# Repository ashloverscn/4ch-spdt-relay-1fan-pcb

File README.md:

# 4ch-spdt-relay-1fan-pcb
4ch-spdt-relay-1fan-pcb

firmware written in arduino :

https://github.com/ashloverscn/ArduinoNano-4ch_Relay_and_1_Fan

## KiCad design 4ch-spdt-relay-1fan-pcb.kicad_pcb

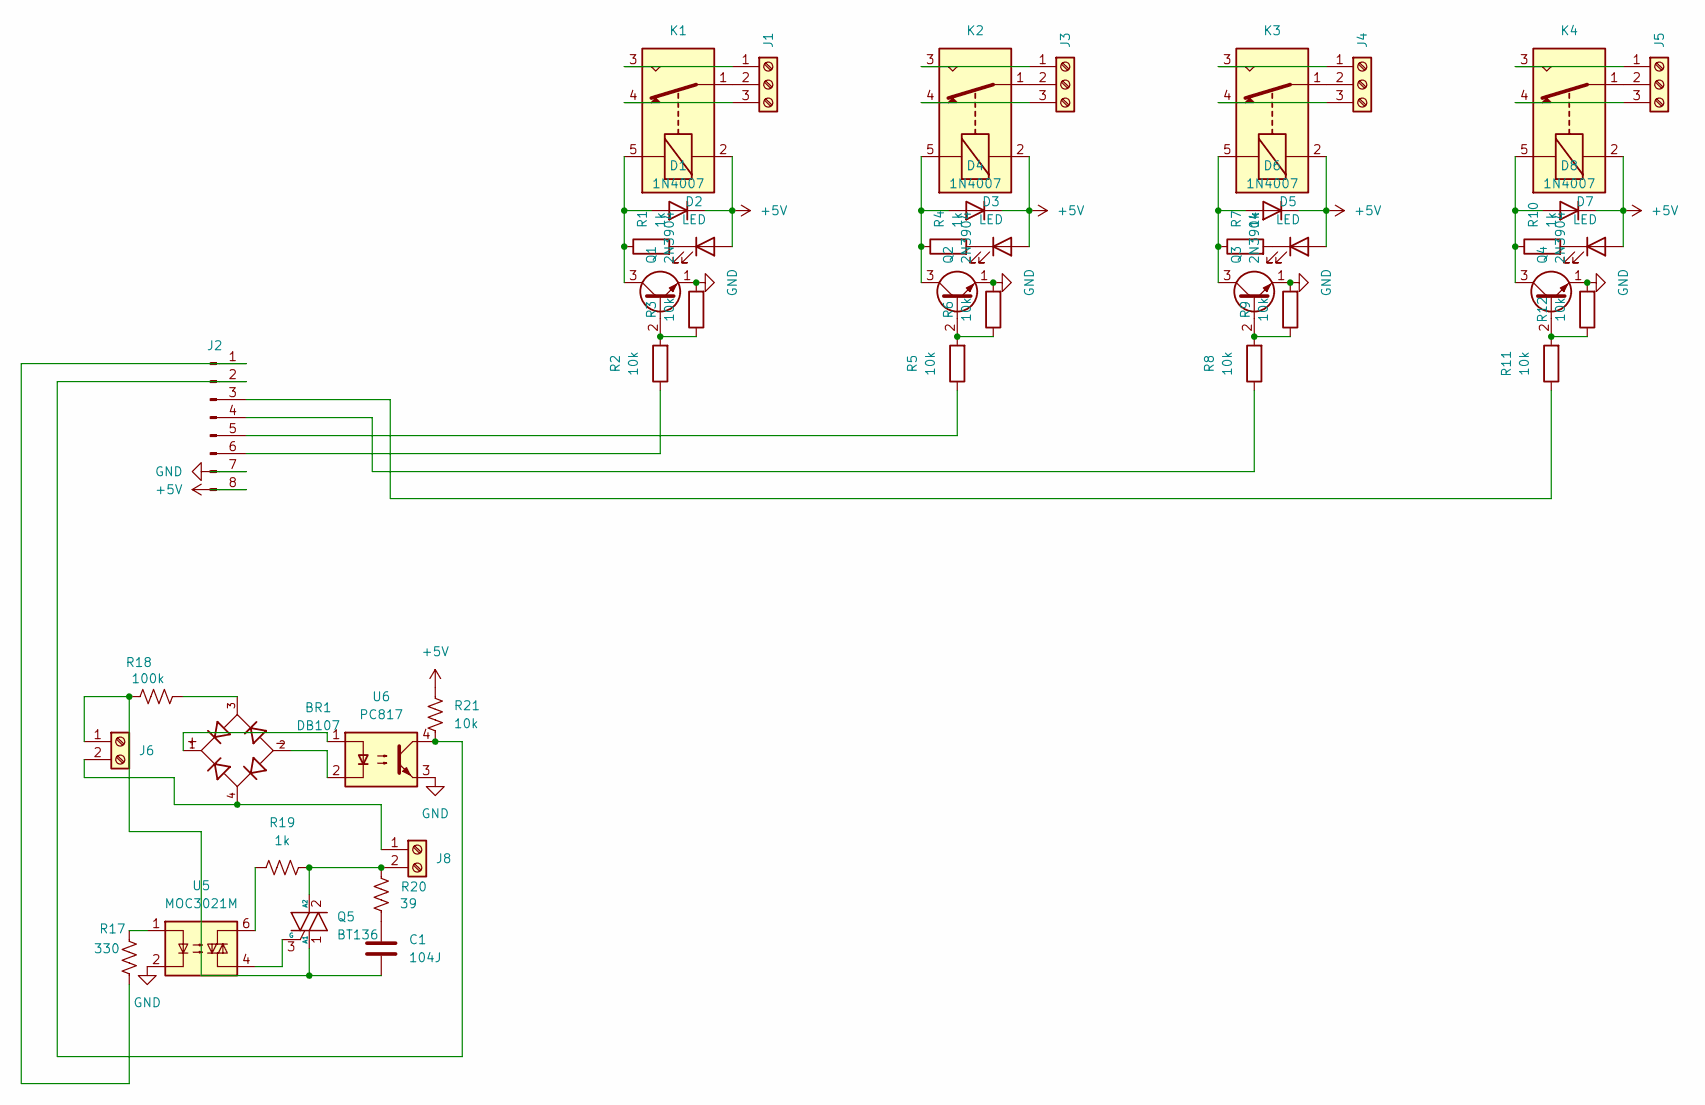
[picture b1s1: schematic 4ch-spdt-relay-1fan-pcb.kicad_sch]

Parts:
BR1: DB107; DIP825W50P509L880H320Q4; PARTREV 13
C1: 104J; C_Disc_D16.0mm_W5.0mm_P10.00mm
D1, D4, D6, D8: 1N4007; D_DO-41_SOD81_P10.16mm_Horizontal
D2, D3, D5, D7: LED; LED_D5.0mm
J1, J3, J4, J5: Screw_Terminal_01x03; TerminalBlock_Phoenix_MKDS-1,5-3-5.08_1x03_P5.08mm_Horizont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
J2: Conn_01x08_Pin; PinHeader_1x08_P2.54mm_Vertical
J6, J8: TerminalBlock_Phoenix_MKDS-1,5-2-5.08_1x02_P5.08mm_Horizont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
K1, K2, K3, K4: G5LE-1; Relay_SPDT_Omron-G5LE-1
Q1, Q2, Q3, Q4: 2N3904; TO-92_Inline
Q5: BT136; TO-220-3_Vertical
R1, R4, R7, R10: 1k; R_Axial_DIN0204_L3.6mm_D1.6mm_P2.54mm_Vertical
R2, R3, R5, R6, R8, R9, R11, R12: 10k; R_Axial_DIN0204_L3.6mm_D1.6mm_P2.54mm_Vertical
R17: 330; R_Axial_DIN0207_L6.3mm_D2.5mm_P2.54mm_Vertical
R18: 100k; R_Axial_DIN0207_L6.3mm_D2.5mm_P5.08mm_Vertical
R19: 1k; R_Axial_DIN0207_L6.3mm_D2.5mm_P2.54mm_Vertical
R20: 39; R_Axial_DIN0207_L6.3mm_D2.5mm_P5.08mm_Vertical
R21: 10k; R_Axial_DIN0207_L6.3mm_D2.5mm_P2.54mm_Vertical
U5: MOC3021M; DIP-6_W7.62mm_LongPads
U6: PC817; DIP-4_W7.62mm_LongPads

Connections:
+5V: D1.1 (K), D2.2 (A), D3.2 (A), D4.1 (K), D5.2 (A), D6.1 (K), D7.2 (A), D8.1 (K), J2.8, K1.2, K2.2, K3.2, K4.2, R21.1
GND: J2.7, Q1.1 (E), Q2.1 (E), Q3.1 (E), Q4.1 (E), R3.2, R6.2, R9.2, R12.2, U5.2, U6.3
unnamed: BR1.1, U6.1
unnamed: BR1.2, U6.2
unnamed: BR1.3, R18.2
unnamed: C1.1, R20.2
unnamed: D1.2 (A), K1.5, Q1.3 (C), R1.1
unnamed: D2.1 (K), R1.2
unnamed: D3.1 (K), R4.2
unnamed: D4.2 (A), K2.5, Q2.3 (C), R4.1
unnamed: D5.1 (K), R7.2
unnamed: D6.2 (A), K3.5, Q3.3 (C), R7.1
unnamed: D7.1 (K), R10.2
unnamed: D8.2 (A), K4.5, Q4.3 (C), R10.1
unnamed: J1.1, K1.3
unnamed: J1.2, K1.1
unnamed: J1.3, K1.4
unnamed: J2.1, R17.2
unnamed: J2.2, R21.2, U6.4
unnamed: J2.3, R11.1
unnamed: J2.4, R8.1
unnamed: J2.5, R5.1
unnamed: J2.6, R2.1
unnamed: J3.1, K2.3
unnamed: J3.2, K2.1
unnamed: J3.3, K2.4
unnamed: J4.1, K3.3
unnamed: J4.2, K3.1
unnamed: J4.3, K3.4
unnamed: J5.1, K4.3
unnamed: J5.2, K4.1
unnamed: J5.3, K4.4
unnamed: C1.2, J6.1, Q5.1 (A1), R18.1
unnamed: BR1.4, J6.2, J8.1
unnamed: J8.2, Q5.2 (A2), R19.1, R20.1
unnamed: Q1.2 (B), R2.2, R3.1
unnamed: Q2.2 (B), R5.2, R6.1
unnamed: Q3.2 (B), R8.2, R9.1
unnamed: Q4.2 (B), R11.2, R12.1
unnamed: Q5.3 (G), U5.4
unnamed: R17.1, U5.1
unnamed: R19.2, U5.6

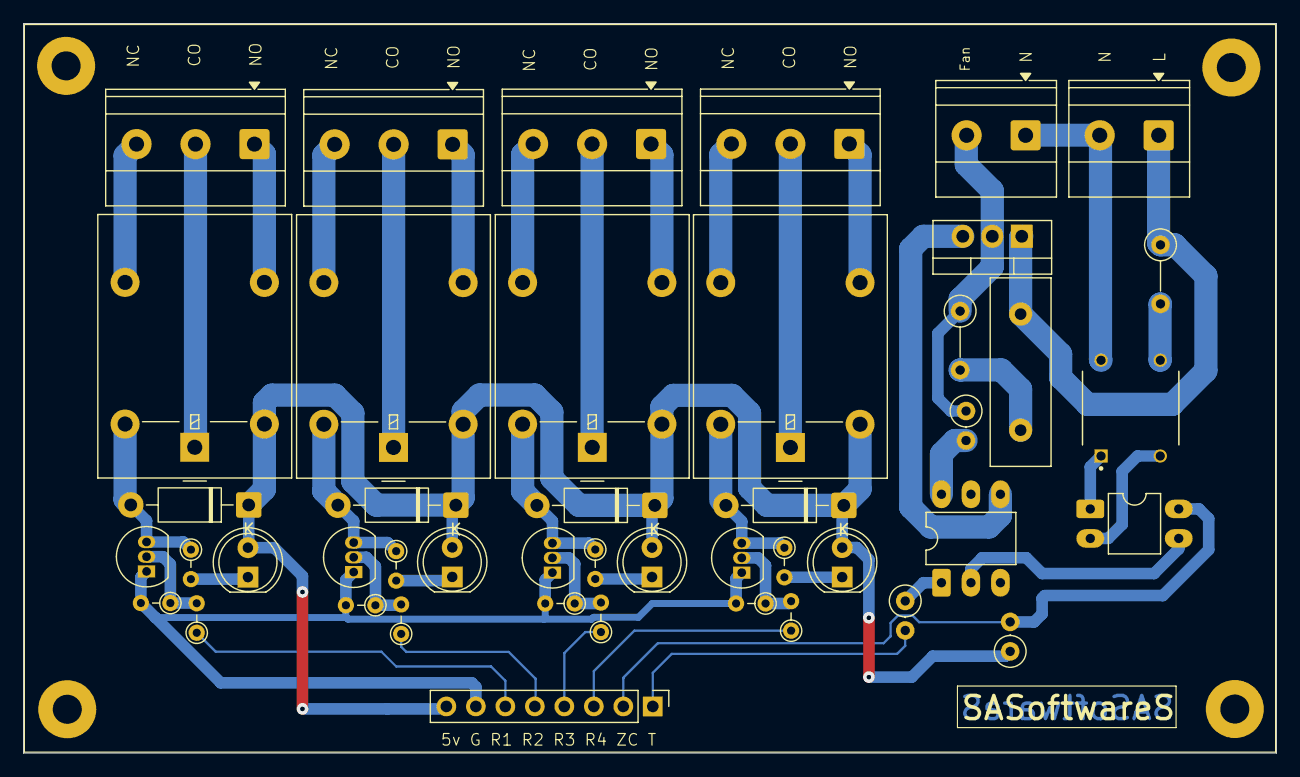
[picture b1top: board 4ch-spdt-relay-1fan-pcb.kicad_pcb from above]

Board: 2 copper layers, 107.9 x 62.8 mm, 45 parts (0 on the bottom side), 42 nets.
